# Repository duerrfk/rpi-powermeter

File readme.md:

RPi-Powermeter is a tool for measuring the power consumption of devices, in particular, battery-powered mobile devices, with a Raspberry Pi. RPi-Powermeter consists of a hardware and software part. The hardware is a board for measuring and sampling the voltage and current of the device using a 12 bit analog-to-digital converter (ADC) connected to the Raspberry Pi through SPI. The software runs on a Raspberry Pi with realtime extension (RT PREEMPT patch) to poll samples from the ADC with defined sampling frequency and log them concurrently to SD card for later post-processing. 

The key features of RPi-Powermeter are:

* Sampling of voltages up to 5 V and current up to 1 A to calculate the power consumption of the device under test (P = U*I). These ranges can be easily adapted by changing the values of only few hardware components (resistors and capacitors).
* Deterministic sampling frequency up to 1 kHz and concurrent data logging with single-core Raspberry Pi.
* Two alternative measurement boards using different methods to measure current, namely, a Hall sensor or shunt resistor. 
* Besides the power supply for the Raspberry Pi, no extra power supply is required. If the Raspberry Pi is powered from a battery pack, the measurement tool can be mobile to facilitate the evaluation of the energy efficiency of mobile devices.
* Simple hardware design (single-sided PCB, through-hole design) to simplify building measurement boards.
* Fully open source hardware and software design with liberal licensing (Apache License 2.0 and CERN Open Hardware License 1.2).

The following figure shows a measurement board with a Hall sensor connected to the Raspberry Pi.

RPi-Powermeter was designed at University of Stuttgart for measuring the power consumption of mobile devices like smartphones to evaluate their energy-efficiency. We publish the design of RPi-Powermeter hoping that it will be useful also for others.

# Hardware: The Measurement Board

The measurement board contains the hardware to sample voltage V and current I of the device under test to calculate the power consumption as P = U*I. There are two versions of the measurement board, using different methods to measure current:

* Hall sensor: this board uses the ACS712 hall sensor, which outputs a voltage proportional to the current flowing through the sensor.  
* Shunt resistor: this board uses a 0.01 Ohm shunt resistor to measure the voltage drop along the resistor, which according to Ohm's law R = U/I is proportional to the current flowing through the shunt.

Both boards are dimensioned to measure voltages up to 5 V and current up to 1 A. These ranges can be adapted by changing the values of few components. 

Both boards are optimized such that the voltage drop along the current sensor is small to avoid a large variation of voltage at the device. Using the measurement board with 0.01 Ohm shunt resistor, the voltage drop along the shunt resistor is only 10 mV at 1 A. Using the Hall sensor with an internal resistance of 1.2 mOhm, the voltage drop is only 1.2 mV. In addition, we measure the voltage directly at the device rather than the power source to account for the voltage drop along the sensor.

Both boards use the MCP3208 12 bit analog-to-digital converter (ADC) to sample the voltage of the device and its current (actually, the amplified voltage of the hall sensor or shunt resistor). The MCP3208 is connected via SPI to the Raspberry Pi.

Schematics and board layouts for Eagle can be found in directory ```pcb/```.

## Design: Measurement Board with Hall Sensor

The following image shows the measurement board using the ACS712 Hall sensor. 

The ACS712 is on a separate PCB, which is available in slightly different versions from several vendors, so you might have to adapt the connector on the main measurement board to your specific ACS712 board.  

The ACS712 can measure current flowing in both directions through the Hall sensor. The output for I = 0 A is offset by 2.5 V (VCC/2). Since we are only interested in current flowing in one direction ("into" the device), we subtract 2.5 V from the sensor output using an op-amp as voltage subtractor (IC2B). 

After subtracting the 2.5 V offset, we amplify the voltage by a factor of 13.7 to increase the voltage gain of the Hall sensor from 180 mV/A to 2.34 V/A using a second op-amp (IC2C). Since we use a reference voltage of 2.5 V for the ADC, we can cover almost the full voltage range of the ADC assming a maximum current of 1 A. You can adjust this factor for other current ranges by changing the values of the two resistors R11 and R12 (amplification = 1 + R11/R12). If you change R11, you might also want to adjust C5 to adapt the low-pass filter (see below).

Since the output of the ACS712 is quite noisy (100 mA p-p) and to avoid interferences, we use a low-pass filter to reduce the amplification for higher frequencies by adding a capacitor (C5) in parallel to resistor R11 of IC2C. Thus, high frequencies will not be amplified. The cut-off frequency of the low-pass filter is calculated as f = 1 / (2*pi*R11*C5). Since we strive for a maximum sampling frequency of 1 kHz, we set f to 1950 Hz. You can adjust f by changing the value of capacitor C5.

A precise reference voltage of 2.5 V is provided by the LM385 diode (D1). IC1A acts as an impedance converter to provide a low impedance 2.5 V source.

The input voltage is divided by 2 by a voltage divider (resistors R13, R14) since we aim for a voltage range up to 5 V, but the ADC maximum input voltage is 2.5 V. Therefore, you need to multiply voltage samples by 2!

We would also like to note that instead of using the LM324 op-amp, you can also use other op-amps such as the MCP6004. Note that offset of the LM324 increases quite fast if it sinks current. In particular, this is a problem for the subtractor implemented by IC2B. A large offset to GND means that you cannot measure small currents anymore (note that the voltage slope of the Hall sensor is only 180 mV/A). In order to alleviate this problem, we use "pull-down" resistor R3 to avoid sinking significant current by the LM324. This reduces the offset to GND to few mV. This resistor might not be necessary for op-amps with smaller offsets like the MCP6004.

In order to ensure stability, the 10 Ohm resistors R7 and R9 decouple the op-amp outputs from the internal sampling capacitor of the ADC. Such small values will not affect the precision of the ADC.

## Design: Measurement Board with Shunt Resistor

The following image shows the measurement board using a 0.01 Ohm shunt resistor. 

To indirectly measure current, we measure the voltage drop along the shunt resistor, which is connected in series with the device under test. With a 0.01 Ohm shunt resistor, this voltage is intentionally very small to keep the voltage at the device close to the supply voltage. 

For precise measurements, we amplify the voltage of the shunt resistor using an instrumentation amplifier (INA126P) with gain 100. The instrumentation amplifier has a very small offset voltage (100 uV) and high common mode rejection ratio. A small offset voltage is crucial at higher gains since also the offset voltage will be amplified. On the downside, the bandwidth of the instrumentation amplifier is not very high (9 kHz at gain 100, 1.8 kHz at gain 500). Therefore, we restrict the gain of the instrumentation amplifier to 100 to stay well above our desired 1 kHz sampling frequency, and use a second op amp with a small gain of 2.49 to get a total gain of 249 (actually, it is an inverting amplifier with gain -2.49 since the voltage drop along the shunt is negative). With a gain of 249, we get about 2.5 V output at 1 A, which is also the reference voltage of the ADC (MCP6004). The second amplification stage also implements a low pass filter with 2341 Hz cut-off frequency to further remove noise. To adapt the gain or cut-off frequency, change the values of the resistors and the capacitor of the low-pass filter. 

The 2.5 V reference voltage is provided by an LM385 diode. An op amp acts as an impedance converter to provide a low impedance 2.5 V source.     

The input voltage is divided by 2 by a voltage divider since we aim for a voltage range up to 5 V, but the ADC maximum input voltage is 2.5 V. Therefore, you need to multiply voltage samples by 2!

For the instrumentation amplifier and the op amp we need a symmetric power supply with a voltage range large enough to compensate for the rail offsets of the instrumentation amplifier and the op amp. To this end, we added a DC/DC converter, which generates +-12 V from the 5 V provided by the Raspberry Pi (+-5 V should also work). Since the voltage of the 1 W DC/DC converter is specified at a minimum load of 10 %, we also added an LED and resistor to provide a minimum load and at the same time a power indicator. 

# Software

The main software of RPi-Powermeter is the Powermeter command line application. Powermeter polls the ADC at given sampling intervals and logs samples concurrently to SD card. 

## Compiling Powermeter

The source code of Powermeter can be found in directory ```src/```. You can compile it using the following command:

    make powermeter

## Using Powermeter

Powermeter has a number of parameters:

* ```-f SPI_FREQUENCY```: SPI clock rate, e.g., 500000 for 500 kHz SPI clock rate. Since we operate the MCP3208 at 3.3 V, the clock rate should be <= 1 MHz (cf. MCP3208 datasheet).
* ```-s SS_PIN```: SPI slave select pin. The Raspberry Pi has two SS pins called CE0 and CE1. 0 selects CE0; 1 selects CE1. The measurement board uses CE0. 
* ```-a ADC_CHANNEL``` and ```-b ADC_CHANNEL```: ADC channels for voltage and current sampling. The measurement board uses ADC channel 0 for current sampling and ADC channel 1 for voltage sampling. 
* ```-F SAMPLING_FREQUENCY```: Sampling frequency. 1 kHz seems to be a safe upper bound where the Raspberry Pi can still deterministically meet the 1 ms sampling interval. Using much smaller sampling intervals is not reasonable since the measurement board implements a low-pass filter with 2 kHz cut-off frequency.
* ```-o FILE```: Output file for logging samples.

The output file format is CSV (comma-separated values). The first value is the actual timestamp of the samples followed by the raw 12 bit values (0-4095) of the two ADC channels, which need to be translated to V and I (see calibration) to calculate the power consumption P = V*I.

## Design of Powermeter

To ensure that samples are taken at precisely defined time intervals, Powermeter relies on a realtime operating system, namely, Linux with RT PREEMPT patch [1]). We refer to the website [2] to show how to install a RT PREEMPT kernel for Raspberry Pi.

In order to achieve deterministic sampling intervals, it is important to remove I/O operations from the critical path executing time-sensitive operations. To this end, Powermeter uses two threads: the time-sensitive sampling thread runs at high priority to poll the ADC at given time intervals. The logging thread concurrently writes samples to a file on SD card. The logging thread runs at lower priority than the sampling thread. If the logging thread is blocked by a long-running IO operation (for instance, when buffers are flushed to disk), the operating system can assign the CPU to the sampling thread. If the blocking I/O call were on the time-sensitive path in a single thread, it would prevent samples from being taken while this thread is blocked. Thus, multi-threading is beneficial also on a single-core machine! Both threads communicate through a ring buffer, which can hold several seconds of samples at 1 kHz, leaving plenty of time for the logging thread to catch up and write samples to disk. Tests showed that with this separation of realtime sampling and background logging, it is possible to achieve deterministic time bounds with 1 kHz sampling frequency on a single-core Raspberry Pi. 

To interface with the ADC through SPI, we use the bcm2835 library [3]. Using WiringPi [4] instead did not lead to deterministic time-bounds. Therefore, we recommend to use bcm2835 by adding ```-DBCM2835LIB``` to the CFLAGS of the Makefile (default setting).

# Calibration

As any measurement tool, also RPi-Powermeter needs to be calibrated first. In order to calculate power as P = VI, we first must translate raw 12 bit ADC values of ADC channel 0 and 1 to current and voltage values, respectively. To translate voltage samples, it is usually enough to consider that the input voltage is divided by 2 by the voltage divider on the measurement board. Thus, you can calculate voltage as V = (s*2.5V/4096) * 2, where s is the voltage sample. However, if you like you can also use a similar calibration method as described for current next.

For calibrating the translation of samples to current values, we first measure the true current, for instance, using a multimeter for several current values, while logging the ADC output using the powermeter tool. To this end, you can connect a resistor to the load connector of the measurement board and a bench power supply connected to the power connector. For instance, we used a 4.7 Ohm resistor rated for 9 W. Be sure not to exceed the power rating of your resistor and the limits of the measurement board (5 V and 1 A)! For instance, at 4.7 V, a current of 1 A will flow through the resistor, so the power rating of the resistor should be greater than P = 4.7 V * 1 A = 4.7 W. 

Collect a sufficent number of ADC values for each known (true) current value. For instance, at 1 kHz sampling rate you will get 10000 samples after running powermeter for 10 s, which should be more than sufficient. Then, average the ADC values to remove noise. Now, you should have several pairs of (true current value [mA], averaged ADC value), e.g., (0, 116.8604), (101, 376.9123), (201, 673.4908), (302, 983.9772), (400, 1274.473), (500, 1588.119), (600, 1889.262), (700, 2187.948), (800, 2500.642).

The goal is now to derive a linear function 

    y(x) = x*m + c

where x is the ADC value, and y(x) is the current value calculated from the ADC value. To calculate the unknowns m and c, we can use linear regression, for instance, using R [5]:

    $ x<-c(116.8604, 376.9123, 673.4908, 983.9772, 1274.473, 1588.119, 1889.262, 2187.948, 2500.642)
    $ y<-c(0, 101, 201, 302, 400, 500, 600, 700, 800) 
    $ fm <- lm(y~x) 
    $ plot(x, y, type = "p") 
    $ abline(fm, col = "red") 
    $ fm  

The values used in this example are real values collected with a RPi-Powermeter board with Hall sensor. Although this sensor is quite noisy, you will see that the averaged samples fit a linear model quite nicely. 

All measurements, also including values for the shunt-based board, can be found in the folder ```calibration````.

# Evaluation

Finally, we evaluate the performance of both measurement boards with respect to noise. All measurements can be found in the folder ```calibration````. 

We measured a set of ADC values for a constant current of 201 mA for both boards with Hall sensor and shunt resistor, respectively. After calibration, one LSB of the ADC corresponds to about 332 uA for the hall sensor board and 248 uA for the shunt resistor board. The following results show the peak-to-peak values for both sensors: 

* Hall sensor board: min = 261; max = 1210; noise = 315 mA p-p
* Shunt resistor board: min = 763; max = 774; noise = 2.8 mA p-p

Note that the noise of the Hall sensor further increases if we leave out the low-pass filter. The depicted values are with low-pass filter.

In conclusion, the measurement board with the shunt resistor exhibits much lower noise and, thus, should be preferred as long as the main feature of the hall sensor (isolation of the power supply of the device under test from the measurement circuit/Raspberry Pi) is not required.

# References

* [1] RT PREEMPT: https://rt.wiki.kernel.org/index.php/Main_Page
* [2] Raspberry Pi Going Realtime with RT Preempt: http://www.frank-durr.de/?p=203
* [3] bcm2825 library: http://www.airspayce.com/mikem/bcm2835/ 
* [4] Wiring Pi library: http://wiringpi.com/
* [5] The R Project: https://www.r-project.org/

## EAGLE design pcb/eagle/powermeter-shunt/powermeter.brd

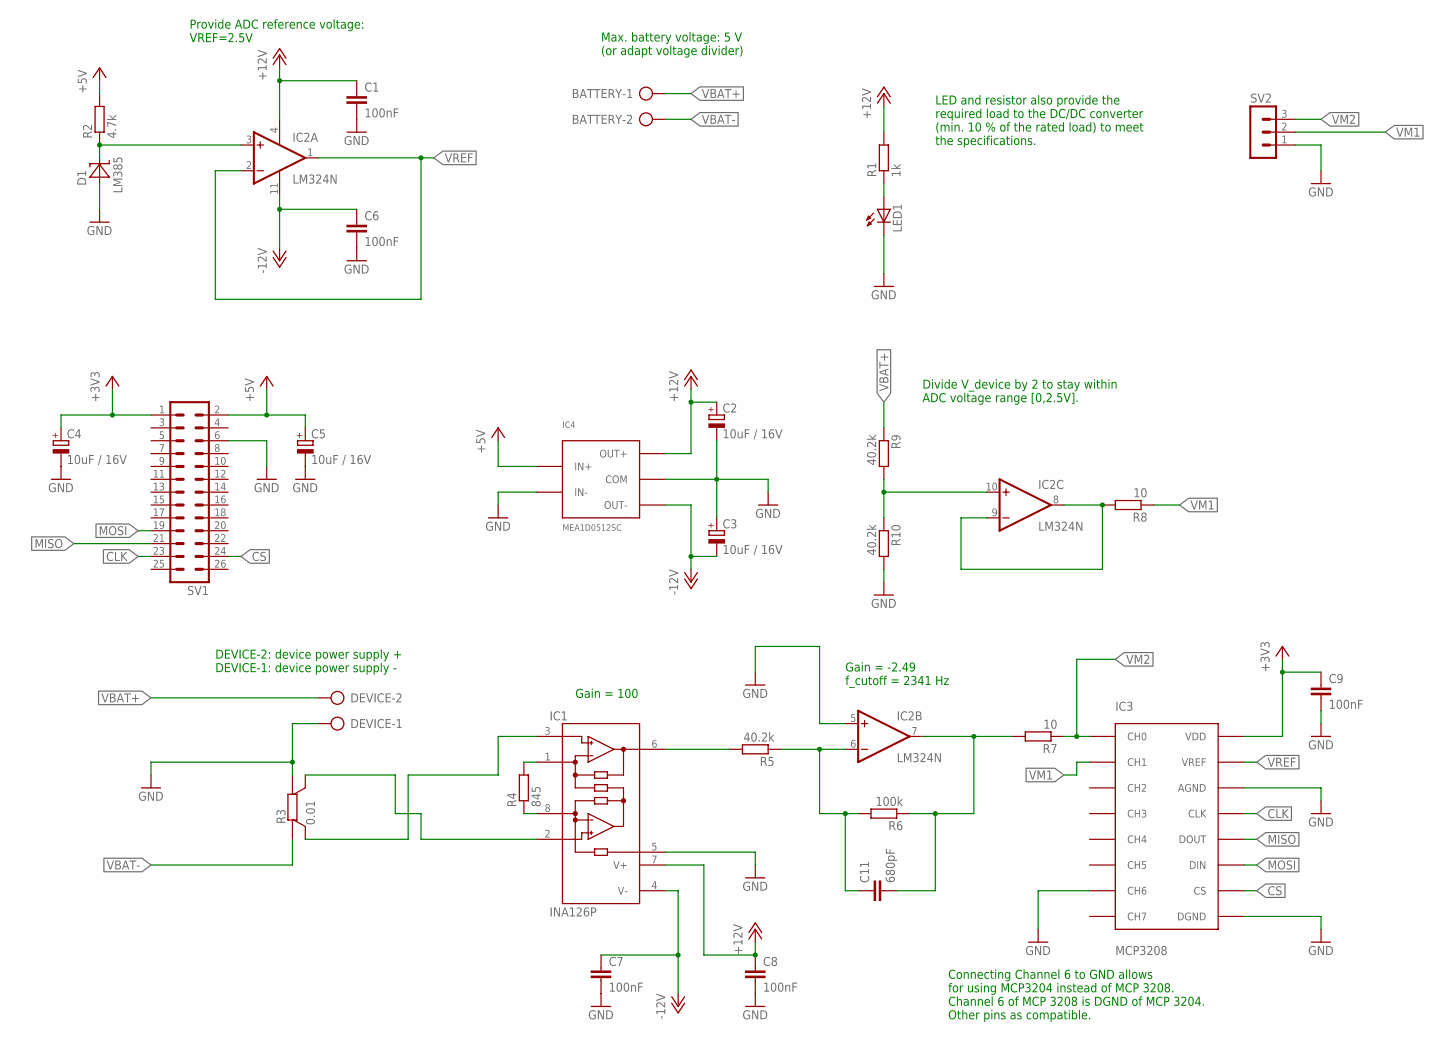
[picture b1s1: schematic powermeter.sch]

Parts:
BATTERY: AK500/2
C1, C6, C7, C8, C9: 100nF; C050-024X044
C2, C3, C4, C5: 10uF / 16V; E2,5-6
C11: 680pF; C050-050X075
D1: LM385; TO-92
DEVICE: AK500/2
IC1: INA126P; DIL08
IC2: LM324N; DIL14
IC3: MCP3208; DIL16
IC4: MEA1D0512SC; MEA1
LED1: LED3MM
R1: 1k; 0207/7
R2: 4.7k; 0207/7
R3: 0.01; PBV
R4: 845; 0207/7
R5, R9, R10: 40.2k; 0207/7
R6: 100k; 0207/7
R7, R8: 10; 0207/7
SV1: ML26
SV2: MA03-1

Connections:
+3V3: C4.+, C9.1, IC3.VDD, SV1.1
+5V: C5.+, IC4.P$IN+ (IN+), R2.2, SV1.2
+12V: C1.1, C2.+, C8.1, IC1.7 (V+), IC2.4 (V+), IC4.P$OUT+ (OUT+), R1.2
-12V: C3.-, C6.1, C7.1, IC1.4 (V-), IC2.11 (V-), IC4.P$OUT- (OUT-)
CLK: IC3.CLK, SV1.23
CS: IC3.CS, SV1.24
GND: C1.2, C2.-, C3.+, C4.-, C5.-, C6.2, C7.2, C8.2, C9.2, D1.+, DEVICE.1, IC1.5 (REF), IC2.5 (+IN), IC3.AGND, IC3.CH6, IC3.DGND, IC4.P$COM (COM), IC4.P$IN- (IN-), LED1.K (C), R3.P$A (A), R10.2, SV1.6, SV2.1
MISO: IC3.DOUT, SV1.21
MOSI: IC3.DIN, SV1.19
unnamed: IC1.1 (RG), R4.2
unnamed: IC1.8 (RG), R4.1
unnamed: IC1.3 (+IN), R3.P$SB (SB)
unnamed: C11.2, IC2.7 (OUT), R6.1, R7.2
unnamed: C11.1, IC2.6 (-IN), R5.1, R6.2
unnamed: IC1.6 (OUT), R5.2
unnamed: IC2.10 (+IN), R9.2, R10.1
unnamed: LED1.A, R1.1
unnamed: IC1.2 (-IN), R3.P$SA (SA)
unnamed: IC2.8 (OUT), IC2.9 (-IN), R8.2
unnamed: D1.-, IC2.3 (+IN), R2.1
VBAT+: BATTERY.1, DEVICE.2, R9.1
VBAT-: BATTERY.2, R3.P$B (B)
VM1: IC3.CH1, R8.1, SV2.2
VM2: IC3.CH0, R7.1, SV2.3
VREF: IC2.1 (OUT), IC2.2 (-IN), IC3.VREF

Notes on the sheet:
Provide ADC reference voltage: VREF=2.5V
DEVICE-2: device power supply + DEVICE-1: device power supply -
Gain = 100
Gain = -2.49 f_cutoff = 2341 Hz
Divide V_device by 2 to stay within ADC voltage range [0,2.5V].
Max. battery voltage: 5 V (or adapt voltage divider)
LED and resistor also provide the required load to the DC/DC converter (min. 10 % of the rated load) to meet the specifications.
Connecting Channel 6 to GND allows for using MCP3204 instead of MCP 3208. Channel 6 of MCP 3208 is DGND of MCP 3204. Other pins as compatible.

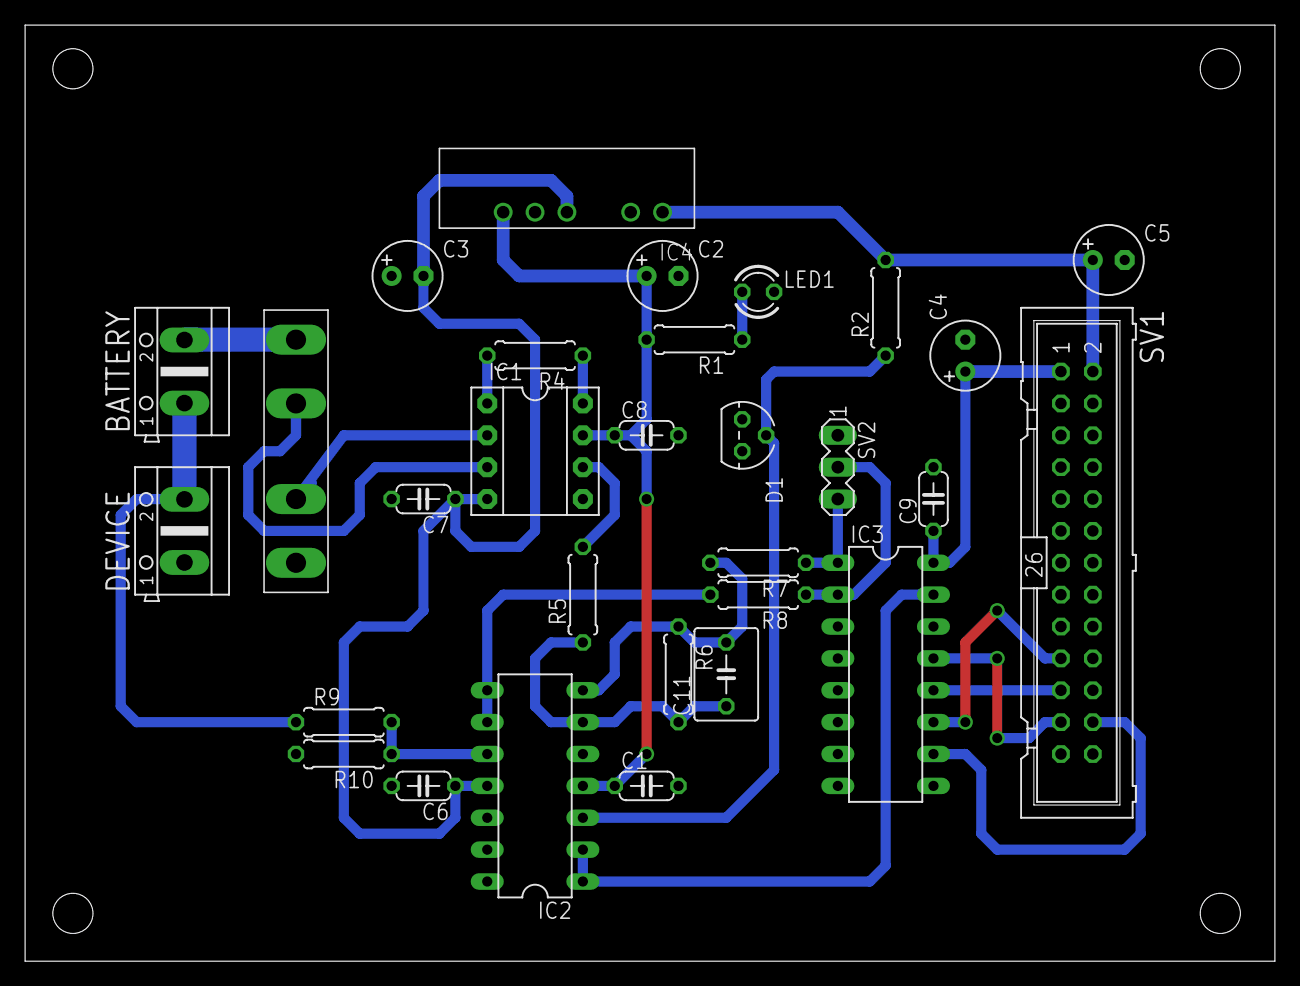
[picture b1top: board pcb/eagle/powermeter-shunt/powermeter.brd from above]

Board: 2 copper layers, 99.6 x 74.6 mm, 30 parts (0 on the bottom side), 25 nets.

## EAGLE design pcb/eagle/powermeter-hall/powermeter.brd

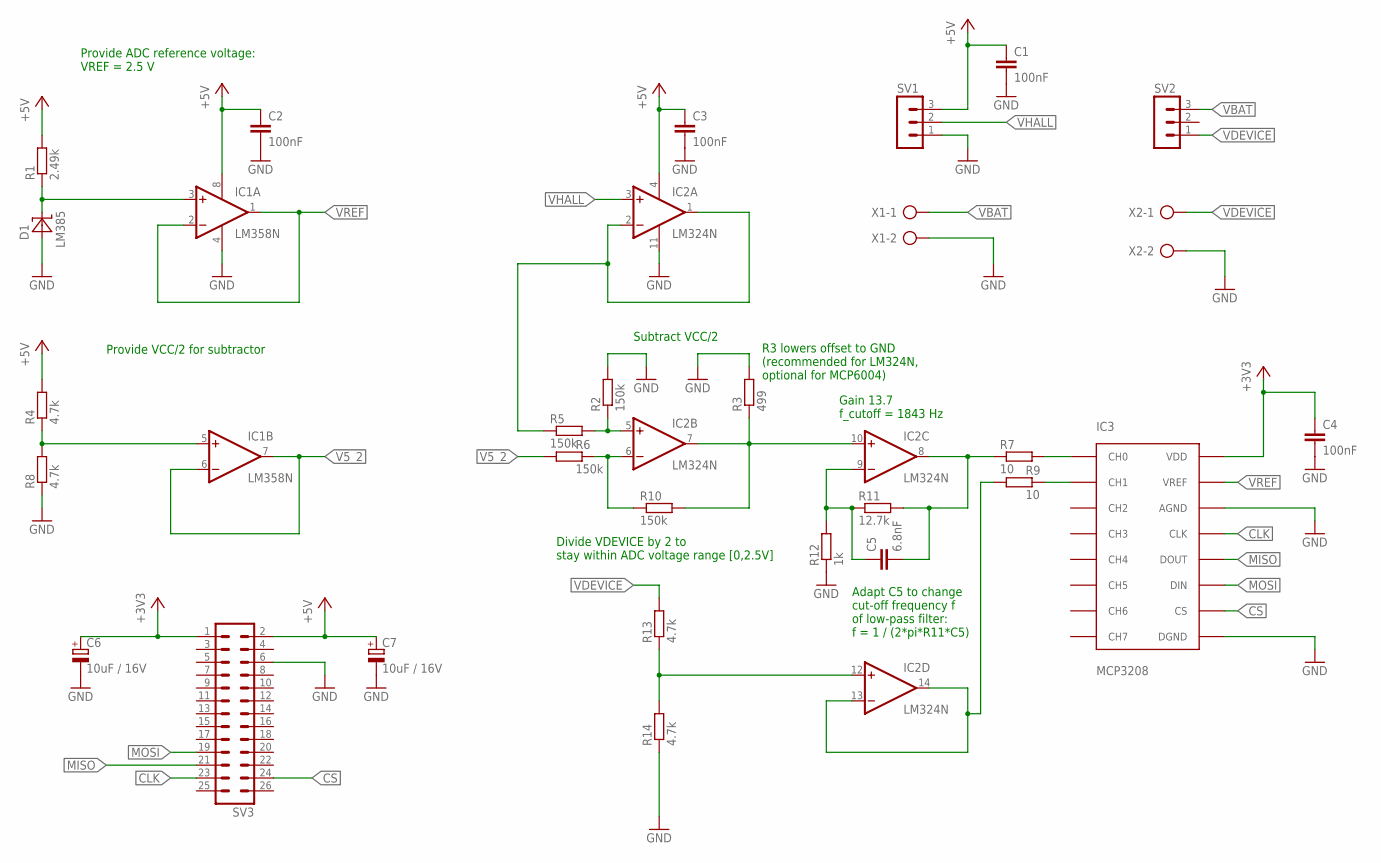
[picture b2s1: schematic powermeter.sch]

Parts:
C1, C2, C3, C4: 100nF; C050-024X044
C5: 6.8nF; C050-030X075
C6, C7: 10uF / 16V; E2,5-5
D1: LM385; TO-92
IC1: LM358N; DIL08
IC2: LM324N; DIL14
IC3: MCP3208; DIL16
R1: 2.49k; 0207/7
R2, R5, R6, R10: 150k; 0207/7
R3: 499; 0207/7
R4, R8, R13, R14: 4.7k; 0207/7
R7, R9: 10; 0207/7
R11: 12.7k; 0207/7
R12: 1k; 0207/7
SV1, SV2: MA03-1
SV3: ML26
X1, X2: AK500/2

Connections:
+3V3: C4.1, C6.+, IC3.VDD, SV3.1
+5V: C1.1, C2.1, C3.1, C7.+, IC1.8 (V+), IC2.4 (V+), R1.2, R4.2, SV1.3, SV3.2
CLK: IC3.CLK, SV3.23
CS: IC3.CS, SV3.24
GND: C1.2, C2.2, C3.2, C4.2, C6.-, C7.-, D1.+, IC1.4 (V-), IC2.11 (V-), IC3.AGND, IC3.DGND, R2.2, R3.2, R8.1, R12.1, R14.1, SV1.1, SV3.6, X1.2, X2.2
MISO: IC3.DOUT, SV3.21
MOSI: IC3.DIN, SV3.19
unnamed: IC1.5 (+IN), R4.1, R8.2
unnamed: C5.2, IC2.8 (OUT), R7.1, R11.2
unnamed: D1.-, IC1.3 (+IN), R1.1
unnamed: IC2.1 (OUT), IC2.2 (-IN), R5.1
unnamed: IC2.5 (+IN), R2.1, R5.2
unnamed: IC2.7 (OUT), IC2.10 (+IN), R3.1, R10.2
unnamed: IC2.6 (-IN), R6.2, R10.1
unnamed: C5.1, IC2.9 (-IN), R11.1, R12.2
unnamed: IC3.CH0, R7.2
unnamed: IC2.12 (+IN), R13.1, R14.2
unnamed: IC2.13 (-IN), IC2.14 (OUT), R9.1
unnamed: IC3.CH1, R9.2
V5_2: IC1.6 (-IN), IC1.7 (OUT), R6.1
VBAT: SV2.3, X1.1
VDEVICE: R13.2, SV2.1, X2.1
VHALL: IC2.3 (+IN), SV1.2
VREF: IC1.1 (OUT), IC1.2 (-IN), IC3.VREF

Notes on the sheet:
Provide ADC reference voltage: VREF = 2.5 V
Provide VCC/2 for subtractor
R3 lowers offset to GND (recommended for LM324N, optional for MCP6004)
Adapt C5 to change cut-off frequency f of low-pass filter: f = 1 / (2*pi*R11*C5)
Subtract VCC/2
Gain 13.7 f_cutoff = 1843 Hz
Divide VDEVICE by 2 to stay within ADC voltage range [0,2.5V]

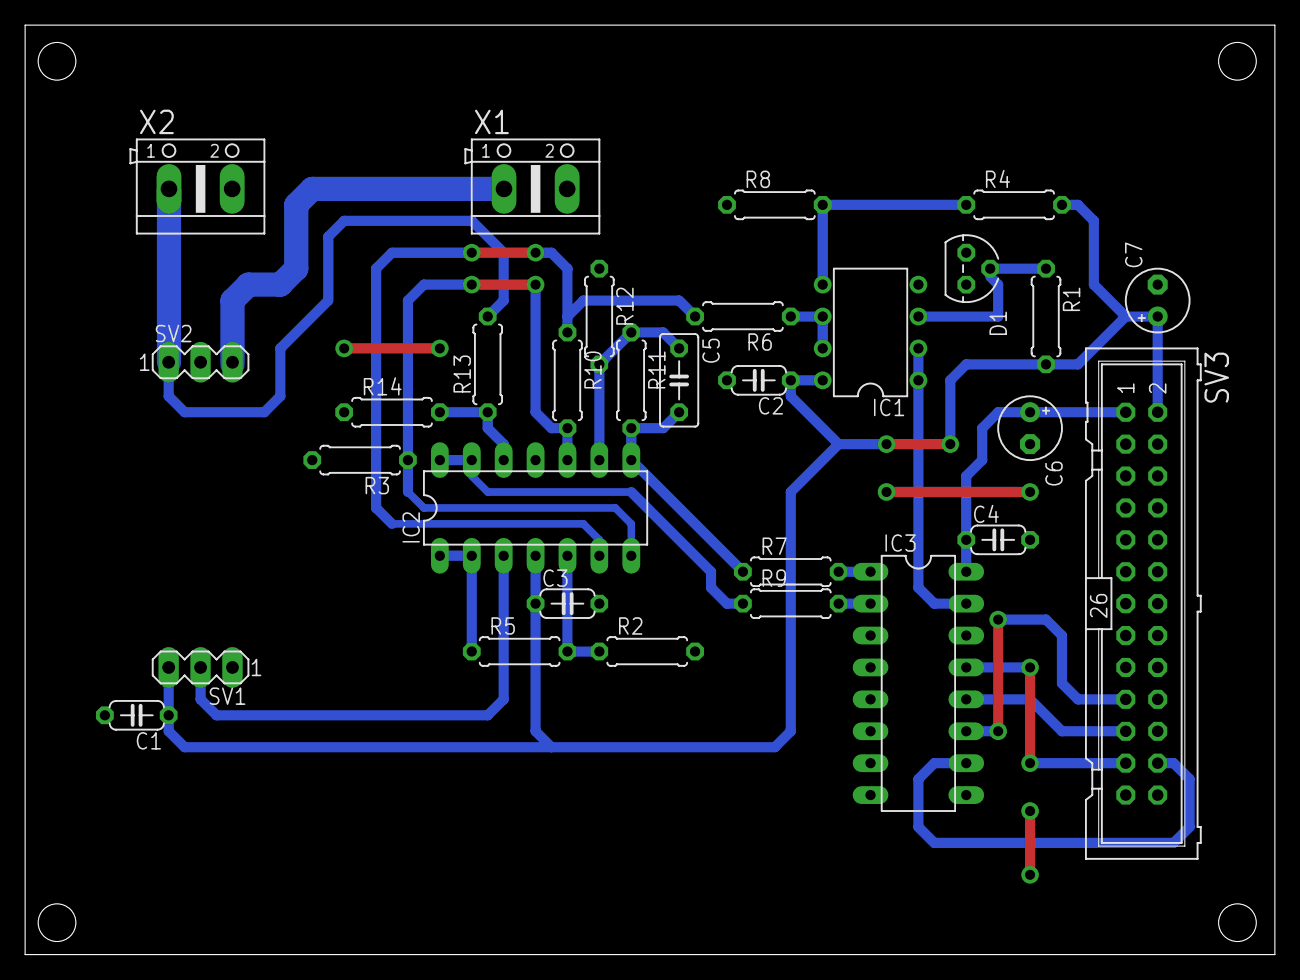
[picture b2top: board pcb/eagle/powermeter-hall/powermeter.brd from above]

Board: 2 copper layers, 99.5 x 74.0 mm, 30 parts (0 on the bottom side), 24 nets.

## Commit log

2016-01-25 Initial check-in
2016-05-26 Made design compatible with MCP3204 (can now use MCP3204 or MCP3208)
2019-08-29 ask if user is root if init fails for bcm2835
2019-08-29 scripts for power consumption, energy consumption, and median filter
